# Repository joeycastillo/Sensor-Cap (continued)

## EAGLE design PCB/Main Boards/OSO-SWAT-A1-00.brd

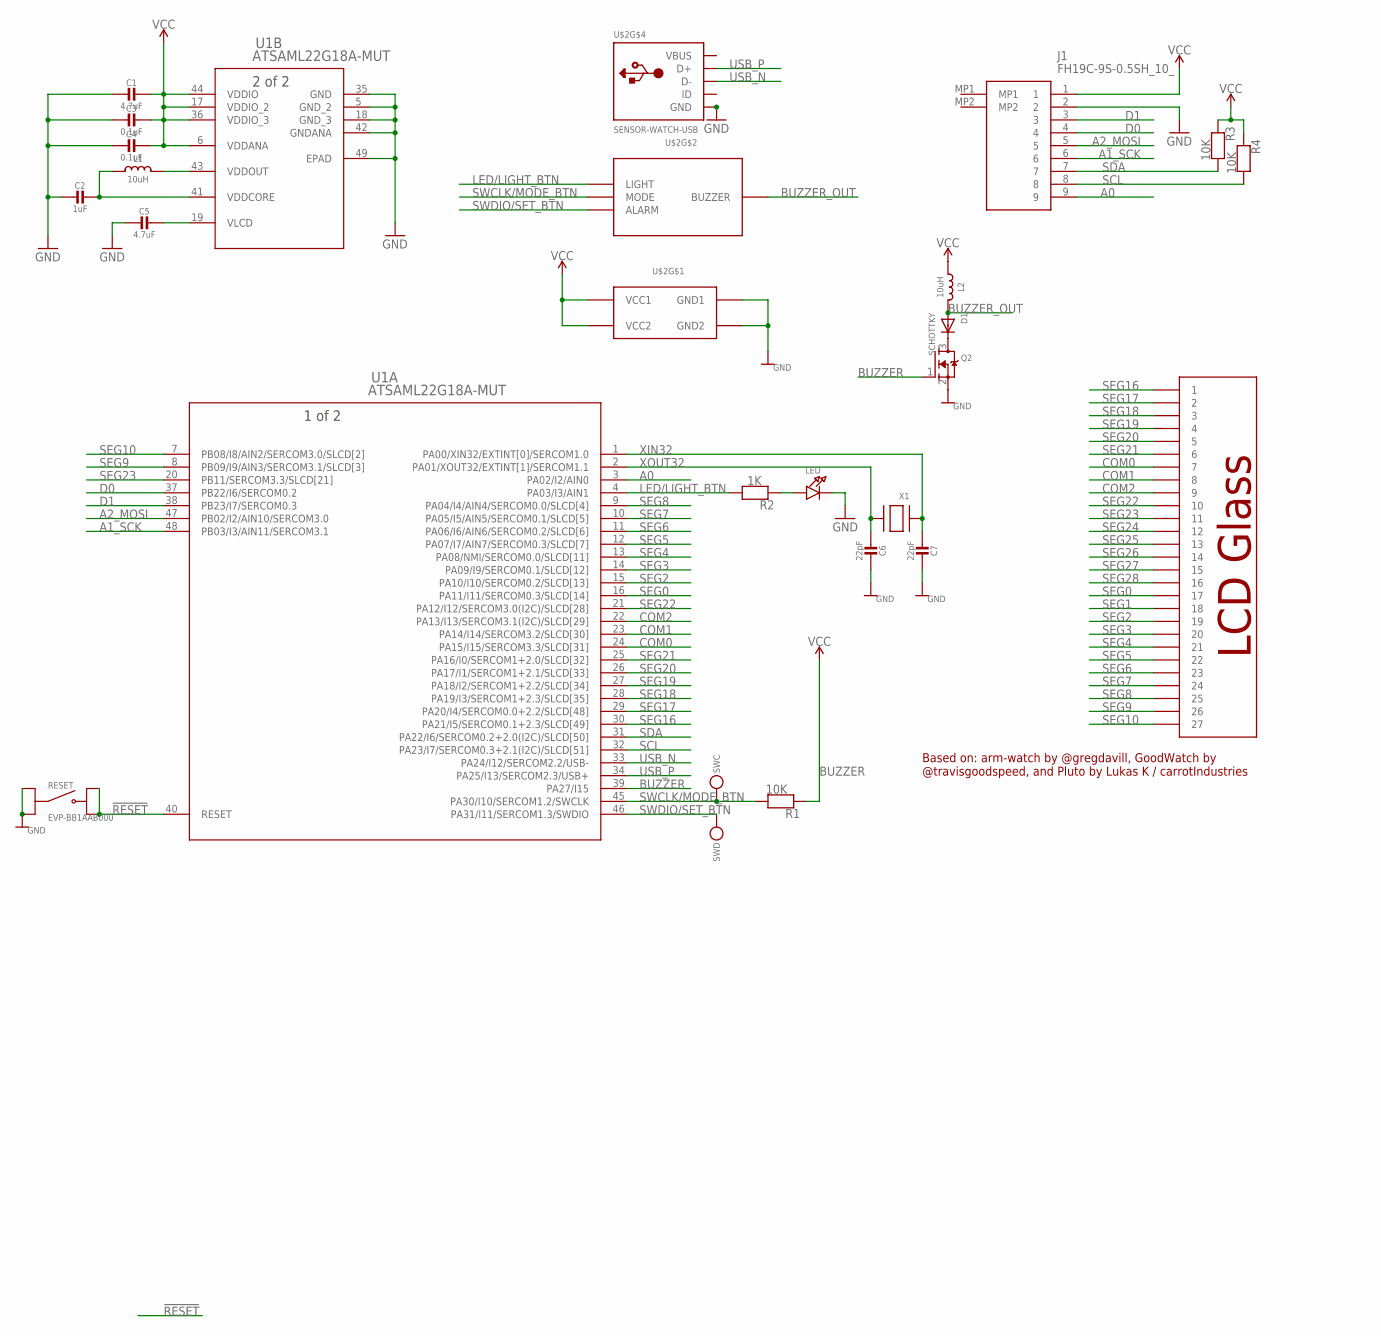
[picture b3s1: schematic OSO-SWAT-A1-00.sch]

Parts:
C1, C5: 4.7uF; _0603MP
C2: 1uF; _0603MP
C3, C4: 0.1uF; _0603MP
C6, C7: 22pF; _0603MP
D1: SCHOTTKY; SOD-323F
J1: FH19C-9S-0.5SH_10_; FH19C9S05SH10
L1, L2: 10uH; MICROBUILDER__0805MP
LED: LED0805_NOOUTLINE; CHIPLED_0805_NOOUTLINE
Q2: MOSFET-NREFLOW; SOT23-R
R1, R3, R4: 10K; _0603MP
R2: 1K; _0603MP
RESET: EVP-BB1AAB000; SW_EVP-BB1AAB000
SWC: MICROBUILDER_TESTPOINTPAD1MM; MICROBUILDER_TESTPOINT_PAD_1MM
SWD: MICROBUILDER_TESTPOINTPAD1MM; MICROBUILDER_TESTPOINT_PAD_1MM
U1: ATSAML22G18A-MUT; QFN48_7X7MC_MCH
U$2: SENSOR-WATCH-USB; CASIO-F91W-OUTLINE-USB
X1: XTAL-3.2X1.5; XTAL3215

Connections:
!RESET: RESET.B1, RESET.B2, U1.40 (RESET)
A0: J1.9, U1.3 (PA02/I2/AIN0)
A1_SCK: J1.6, U1.48 (PB03/I3/AIN11/SERCOM3.1)
A2_MOSI: J1.5, U1.47 (PB02/I2/AIN10/SERCOM3.0)
BUZZER: Q2.1 (G), U1.39 (PA27/I15)
BUZZER_OUT: D1.A, L2.2, U$2.BUZZER
COM0: U1.24 (PA15/I15/SERCOM3.3/SLCD[31]), U$2.7
COM1: U1.23 (PA14/I14/SERCOM3.2/SLCD[30]), U$2.8
COM2: U1.22 (PA13/I13/SERCOM3.1(I2C)/SLCD[29]), U$2.9
D0: J1.4, U1.37 (PB22/I6/SERCOM0.2)
D1: J1.3, U1.38 (PB23/I7/SERCOM0.3)
GND: C1.2, C2.2, C3.2, C4.2, C5.2, C6.2, C7.2, J1.2, LED.C, Q2.2 (S), RESET.A1, RESET.A2, U1.5 (GND_2), U1.18 (GND_3), U1.35 (GND), U1.42 (GNDANA), U1.49 (EPAD), U$2.GND, U$2.GND1, U$2.GND2
LED/LIGHT_BTN: R2.2, U1.4 (PA03/I3/AIN1), U$2.LIGHT
unnamed: LED.A, R2.1
unnamed: D1.C, Q2.3 (D)
SCL: J1.8, R4.2, U1.32 (PA23/I7/SERCOM0.3+2.1(I2C)/SLCD[51])
SDA: J1.7, R3.2, U1.31 (PA22/I6/SERCOM0.2+2.0(I2C)/SLCD[50])
SEG0: U1.16 (PA11/I11/SERCOM0.3/SLCD[14]), U$2.17
SEG1: U$2.18
SEG2: U1.15 (PA10/I10/SERCOM0.2/SLCD[13]), U$2.19
SEG3: U1.14 (PA09/I9/SERCOM0.1/SLCD[12]), U$2.20
SEG4: U1.13 (PA08/NMI/SERCOM0.0/SLCD[11]), U$2.21
SEG5: U1.12 (PA07/I7/AIN7/SERCOM0.3/SLCD[7]), U$2.22
SEG6: U1.11 (PA06/I6/AIN6/SERCOM0.2/SLCD[6]), U$2.23
SEG7: U1.10 (PA05/I5/AIN5/SERCOM0.1/SLCD[5]), U$2.24
SEG8: U1.9 (PA04/I4/AIN4/SERCOM0.0/SLCD[4]), U$2.25
SEG9: U1.8 (PB09/I9/AIN3/SERCOM3.1/SLCD[3]), U$2.26
SEG10: U1.7 (PB08/I8/AIN2/SERCOM3.0/SLCD[2]), U$2.27
SEG16: U1.30 (PA21/I5/SERCOM0.1+2.3/SLCD[49]), U$2.1
SEG17: U1.29 (PA20/I4/SERCOM0.0+2.2/SLCD[48]), U$2.2
SEG18: U1.28 (PA19/I3/SERCOM1+2.3/SLCD[35]), U$2.3
SEG19: U1.27 (PA18/I2/SERCOM1+2.2/SLCD[34]), U$2.4
SEG20: U1.26 (PA17/I1/SERCOM1+2.1/SLCD[33]), U$2.5
SEG21: U1.25 (PA16/I0/SERCOM1+2.0/SLCD[32]), U$2.6
SEG22: U1.21 (PA12/I12/SERCOM3.0(I2C)/SLCD[28]), U$2.10
SEG23: U1.20 (PB11/SERCOM3.3/SLCD[21]), U$2.11
SEG24: U$2.12
SEG25: U$2.13
SEG26: U$2.14
SEG27: U$2.15
SEG28: U$2.16
SWCLK/MODE_BTN: R1.2, SWC.P$1, U1.45 (PA30/I10/SERCOM1.2/SWCLK), U$2.MODE
SWDIO/SET_BTN: SWD.P$1, U1.46 (PA31/I11/SERCOM1.3/SWDIO), U$2.ALARM
USB_N: U1.33 (PA24/I12/SERCOM2.2/USB-), U$2.USB_N (D-)
USB_P: U1.34 (PA25/I13/SERCOM2.3/USB+), U$2.USB_P (D+)
VBUS: U$2.VBUS
VCC: C1.1, C3.1, C4.1, J1.1, L2.1, R1.1, R3.1, R4.1, U1.6 (VDDANA), U1.17 (VDDIO_2), U1.36 (VDDIO_3), U1.44 (VDDIO), U$2.VCC1, U$2.VCC2
VDDCORE: C2.1, L1.1, U1.41 (VDDCORE)
VDDOUT: L1.2, U1.43 (VDDOUT)
VLCD: C5.1, U1.19 (VLCD)
XIN32: C7.1, U1.1 (PA00/XIN32/EXTINT[0]/SERCOM1.0), X1.P$1
XOUT32: C6.1, U1.2 (PA01/XOUT32/EXTINT[1]/SERCOM1.1), X1.P$2

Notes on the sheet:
Based on: arm-watch by @gregdavill, GoodWatch by @travisgoodspeed, and Pluto by Lukas K / carrotIndustries

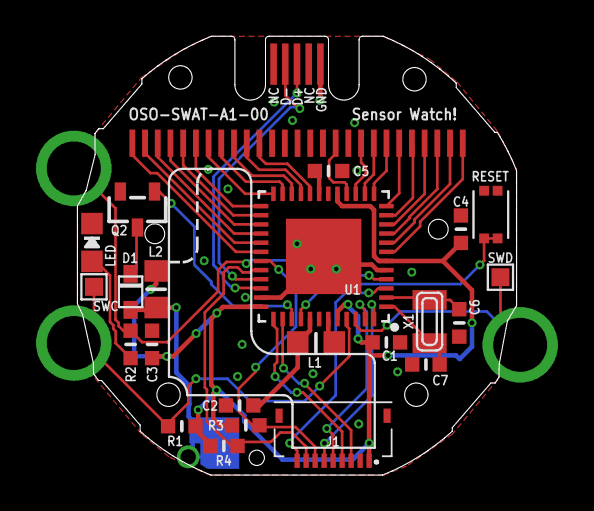
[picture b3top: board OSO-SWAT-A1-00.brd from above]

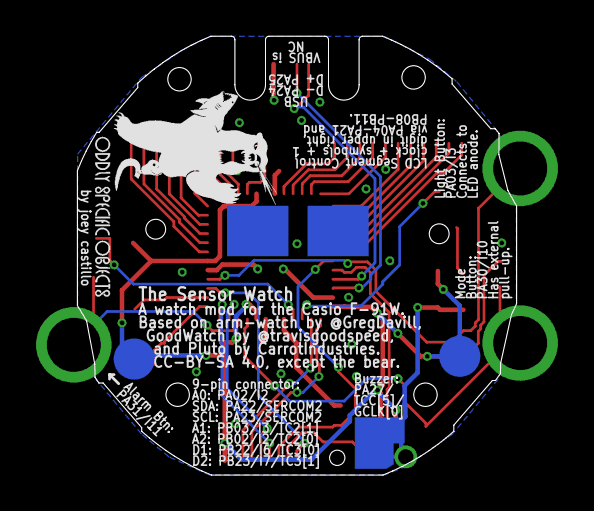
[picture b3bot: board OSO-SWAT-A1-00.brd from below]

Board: 2 copper layers, 24.4 x 24.4 mm, 25 parts (2 on the bottom side), 45 nets.

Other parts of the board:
U$5: OSO_BEAR_250X360MIL_1000DPI
U$6: OSO_WORDMARK_ONELINE_350MIL_1000DPI

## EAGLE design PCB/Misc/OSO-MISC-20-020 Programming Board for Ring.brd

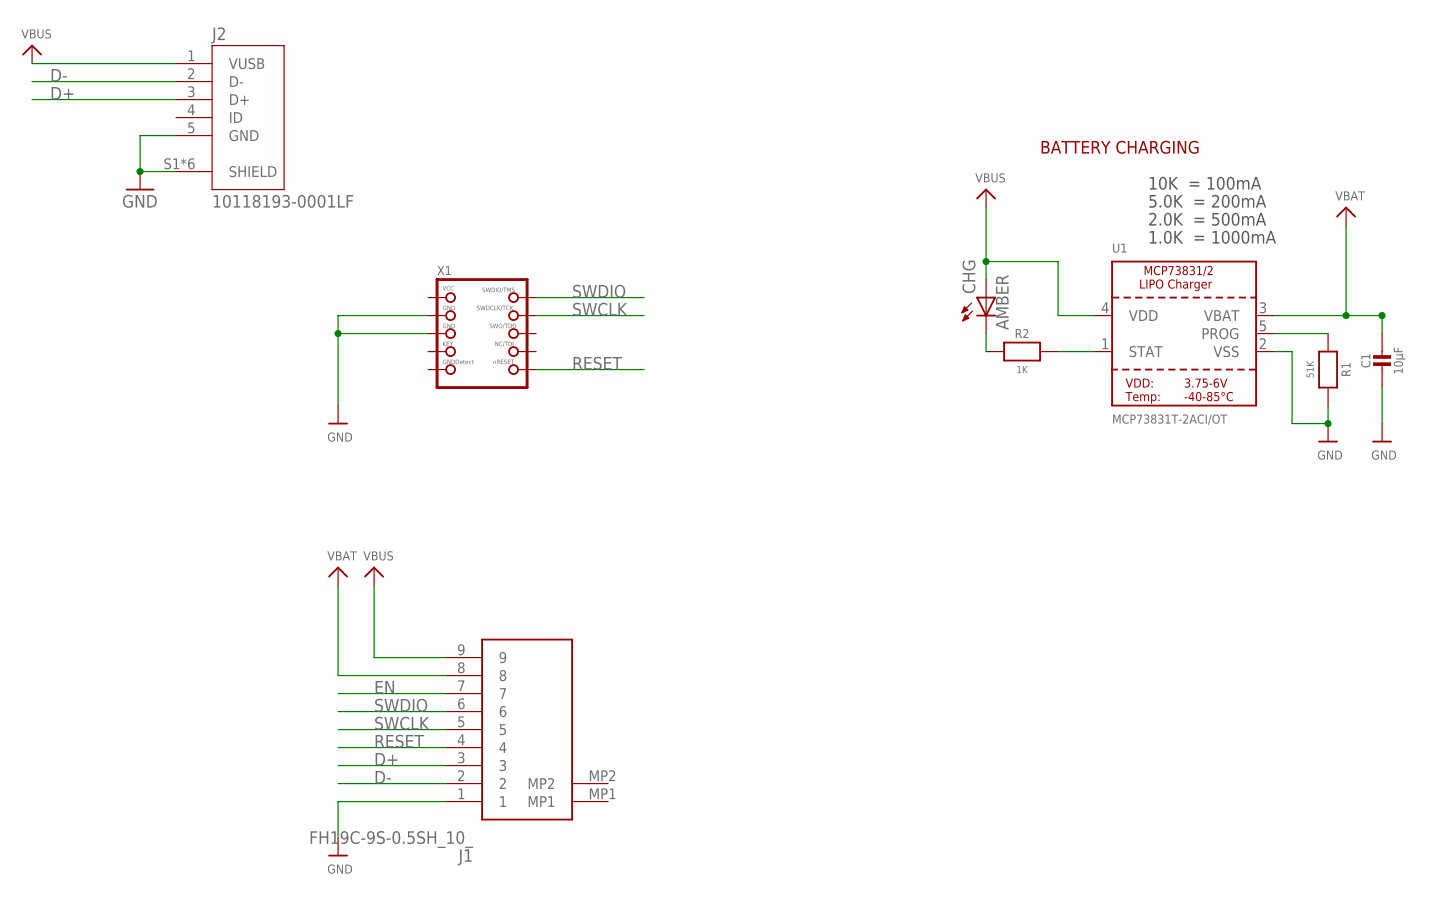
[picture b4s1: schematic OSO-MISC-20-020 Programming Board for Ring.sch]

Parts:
C1: 10µF; 0805-NO
CHG: AMBER; CHIPLED_0805
J1: FH19C-9S-0.5SH_10_; FH19C9S05SH10
J2: 10118193-0001LF; FCI_10118193-0001LF
R1: 51K; 0805-NO
R2: 1K; 0805-NO
U1: MCP73831T-2ACI/OT; SOT23-5
X1: JTAG-CORTEXBOX; 2X05_1.27MM_BOX_NOPOSTS

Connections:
D+: J1.3, J2.3 (D+)
D-: J1.2, J2.2 (D-)
EN: J1.7
GND: C1.2, J1.1, J2.5 (GND), J2.S1 (SHIELD), J2.S2 (SHIELD), J2.S3 (SHIELD), J2.S4 (SHIELD), J2.S5 (SHIELD), J2.S6 (SHIELD), R1.2, U1.2 (VSS), X1.3 (GND), X1.5 (GND)
unnamed: CHG.C, R2.1
PROG: R1.1, U1.5 (PROG)
RESET: J1.4, X1.10 (NRESET)
STAT: R2.2, U1.1 (STAT)
SWCLK: J1.5, X1.4 (SWDCLK)
SWDIO: J1.6, X1.2 (SWDIO)
VBAT: C1.1, J1.8, U1.3 (VBAT)
VBUS: CHG.A, J1.9, J2.1 (VUSB), U1.4 (VDD)
VCC: X1.1 (VCC)

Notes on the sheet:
10K = 100mA
5.0K = 200mA
2.0K = 500mA
1.0K = 1000mA
BATTERY CHARGING

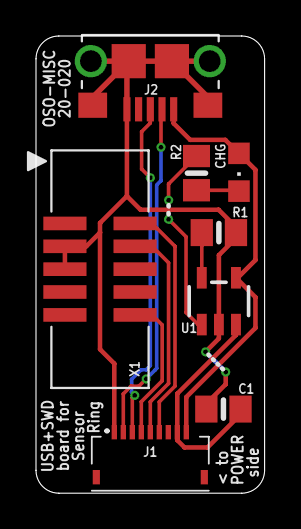
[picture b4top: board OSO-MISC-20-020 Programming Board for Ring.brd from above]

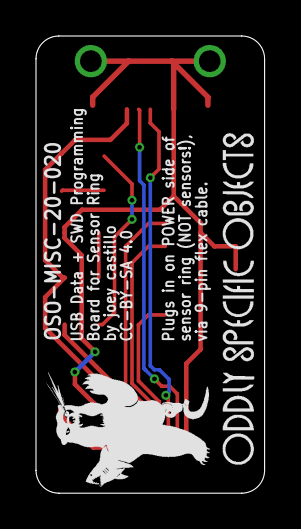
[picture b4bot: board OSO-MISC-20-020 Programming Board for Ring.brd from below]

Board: 2 copper layers, 12.7 x 25.4 mm, 10 parts (2 on the bottom side), 11 nets.

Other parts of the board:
U$1: OSO_BEAR_250X360MIL_1000DPI
U$3: OSO_WORDMARK_ONELINE_725MIL_1000DPI

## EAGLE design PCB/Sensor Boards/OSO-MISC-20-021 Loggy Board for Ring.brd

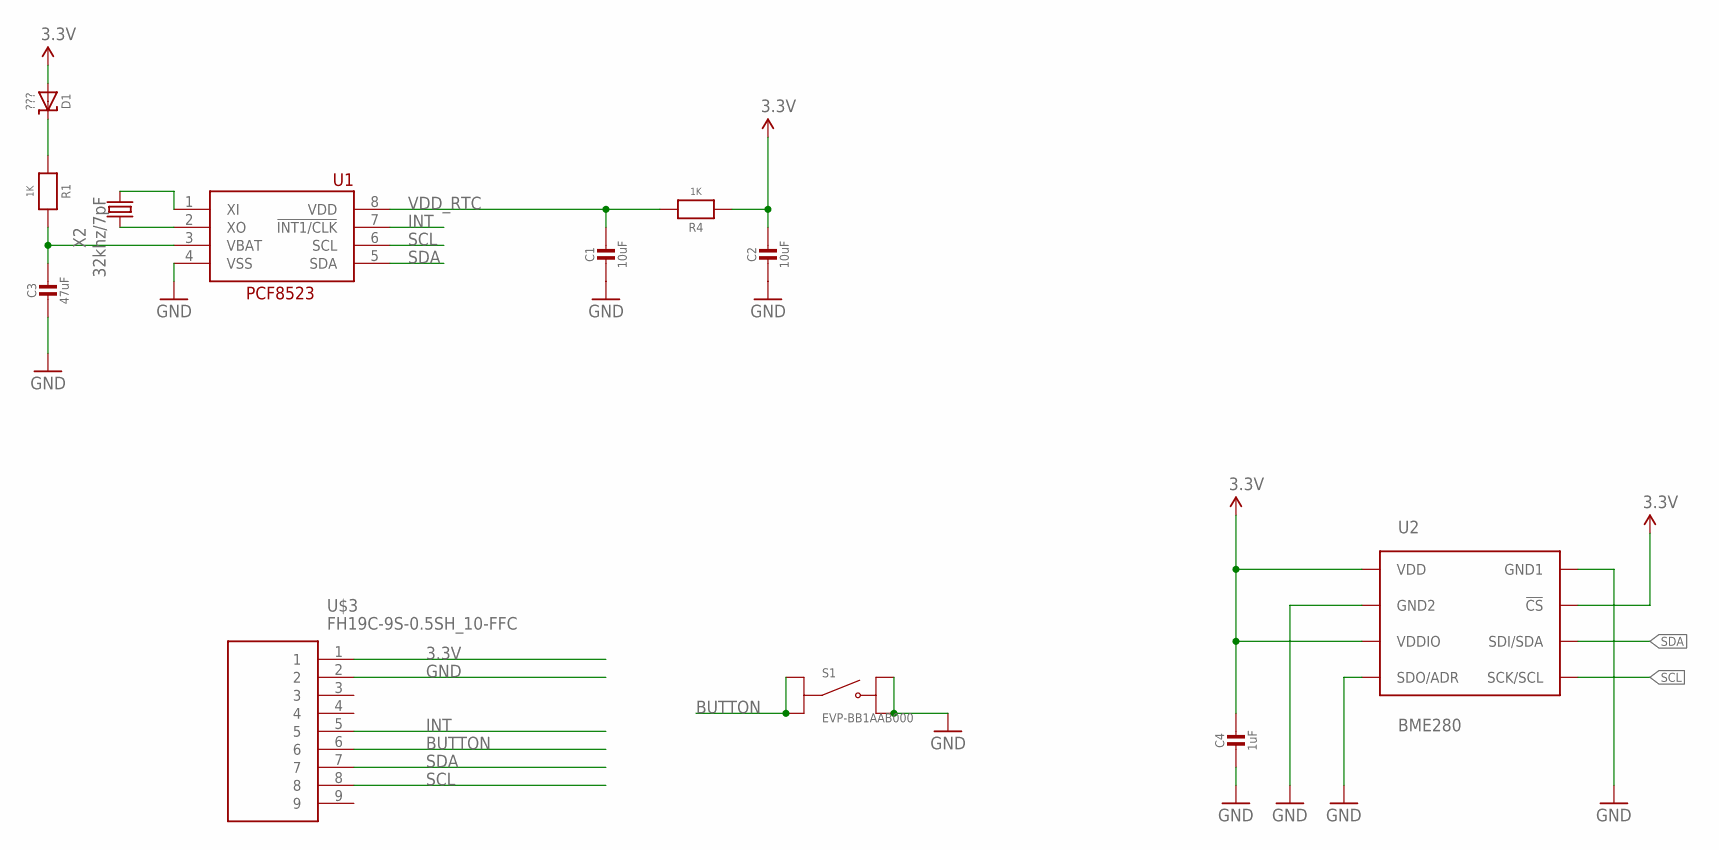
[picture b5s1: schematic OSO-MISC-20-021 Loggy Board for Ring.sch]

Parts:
C1, C2: 10uF; 0805-NO
C3: 47uF; 0805-NO
C4: 1uF; _0805MP
D1: ???; SOD-123
R1, R4: 1K; 0805-NO
S1: EVP-BB1AAB000; SW_EVP-BB1AAB000
U1: PCF8523T; SOIC8_150MIL
U2: BME280; BME280_LGA
U$3: FH19C-9S-0.5SH_10-FFC; FH19C9S05SH10-FFC
X2: 32khz/7pF; XTAL-7015

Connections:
3.3V: C2.1, C4.1, D1.A, R4.1, U2.P$2 (!CS), U2.P$6 (VDDIO), U2.P$8 (VDD), U$3.1
BUTTON: S1.A1, S1.A2, U$3.6
GND: C1.2, C2.2, C3.2, C4.2, S1.B1, S1.B2, U1.4 (VSS), U2.P$1 (GND1), U2.P$5 (SDO/ADR), U2.P$7 (GND2), U$3.2
INT: U1.7 (!INT1/CLK), U$3.5
unnamed: D1.C, R1.1
unnamed: C3.1, R1.2, U1.3 (VBAT)
unnamed: U1.1 (XI), X2.1
unnamed: U1.2 (XO), X2.4 (2)
SCL: U1.6 (SCL), U2.P$4 (SCK/SCL), U$3.8
SDA: U1.5 (SDA), U2.P$3 (SDI/SDA), U$3.7
VDD_RTC: C1.1, R4.2, U1.8 (VDD)

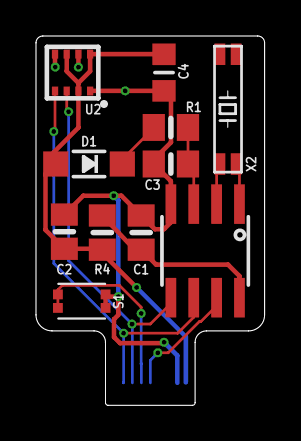
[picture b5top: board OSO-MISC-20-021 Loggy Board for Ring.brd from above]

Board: 2 copper layers, 12.7 x 20.5 mm, 12 parts (0 on the bottom side), 11 nets.

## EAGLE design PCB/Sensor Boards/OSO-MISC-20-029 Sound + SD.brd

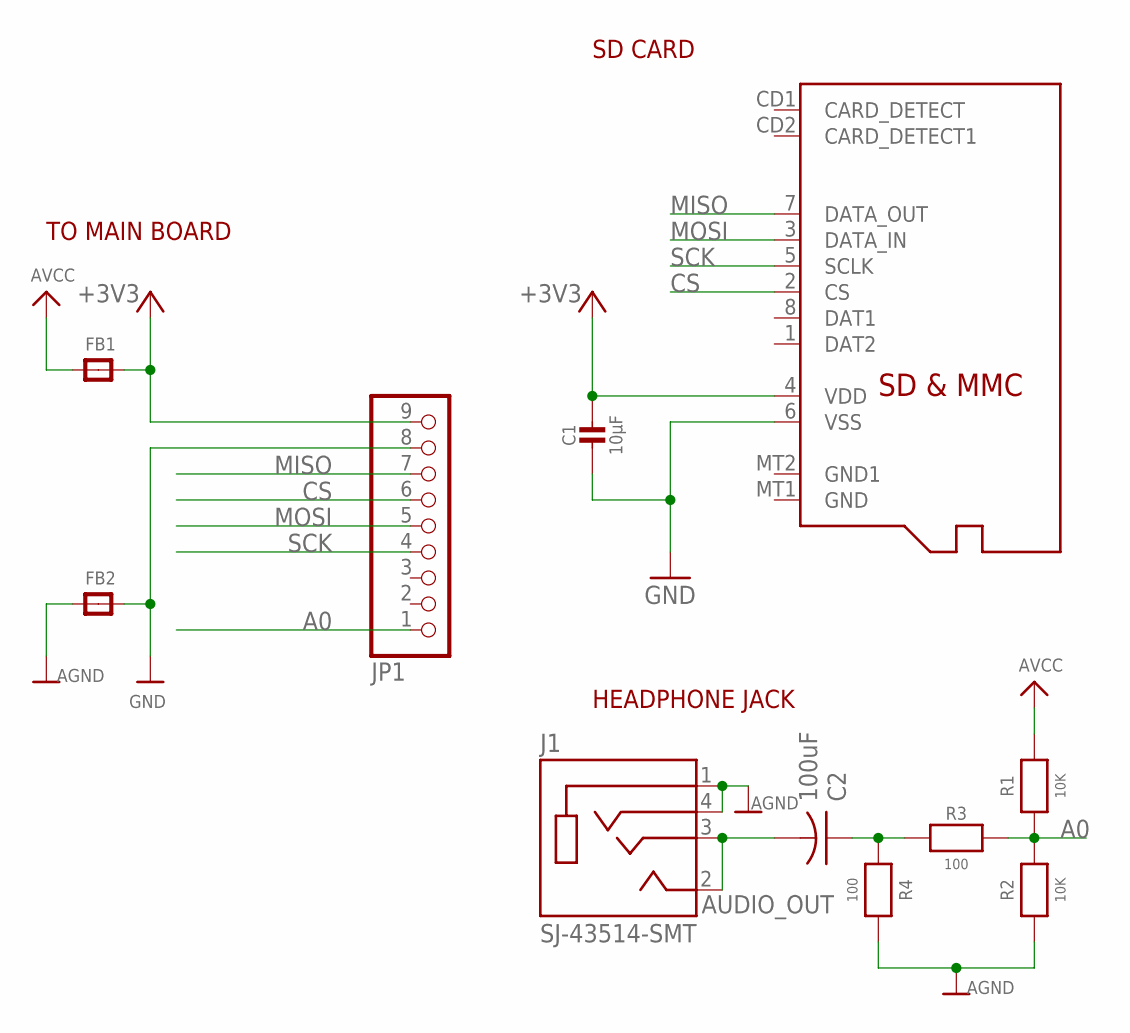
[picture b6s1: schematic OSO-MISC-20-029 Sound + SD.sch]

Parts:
C1: 10µF; 0805-NO
C2: 100uF; C1210
FB1, FB2: FERRITE0805; 0805
J1: SJ-43514-SMT; CUI_SJ-43514-SMT
JP1: HEADER-1X9_JSTSH; JST_SH9
MICROSD: MICROSD
R1, R2: 10K; _0805MP
R3, R4: 100; _0805MP

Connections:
+3V3: C1.1, FB1.2, JP1.9, MICROSD.4 (VDD)
A0: JP1.1, R1.2, R2.1, R3.1
AGND: FB2.1, J1.1 (SLEEVE), J1.4 (RING2), R2.2, R4.1
AUDIO_OUT: C2.2, J1.2 (TIP), J1.3 (RING1)
AVCC: FB1.1, R1.1
CS: JP1.6, MICROSD.2 (CS)
GND: C1.2, FB2.2, JP1.8, MICROSD.6 (VSS)
MISO: JP1.7, MICROSD.7 (DATA_OUT)
MOSI: JP1.5, MICROSD.3 (DATA_IN)
unnamed: C2.1, R3.2, R4.2
SCK: JP1.4, MICROSD.5 (SCLK)

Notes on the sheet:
SD CARD
TO MAIN BOARD
HEADPHONE JACK

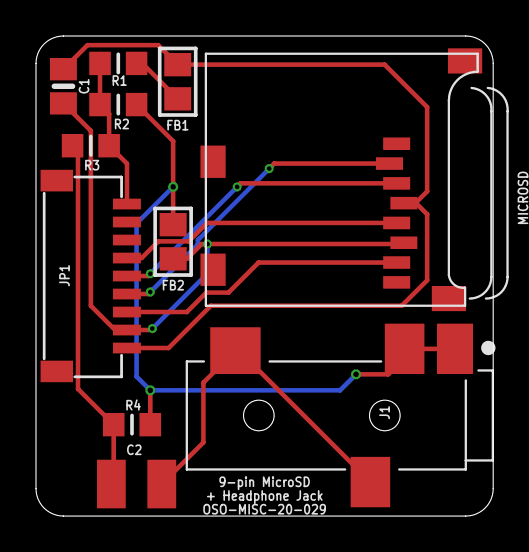
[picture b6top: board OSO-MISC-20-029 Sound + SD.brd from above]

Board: 2 copper layers, 25.4 x 26.7 mm, 13 parts (2 on the bottom side), 11 nets.

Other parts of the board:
U$4: OSO_BEAR_525X750MIL_1000DPI
U$5: OSO_WORDMARK_ONELINE_725MIL_1000DPI

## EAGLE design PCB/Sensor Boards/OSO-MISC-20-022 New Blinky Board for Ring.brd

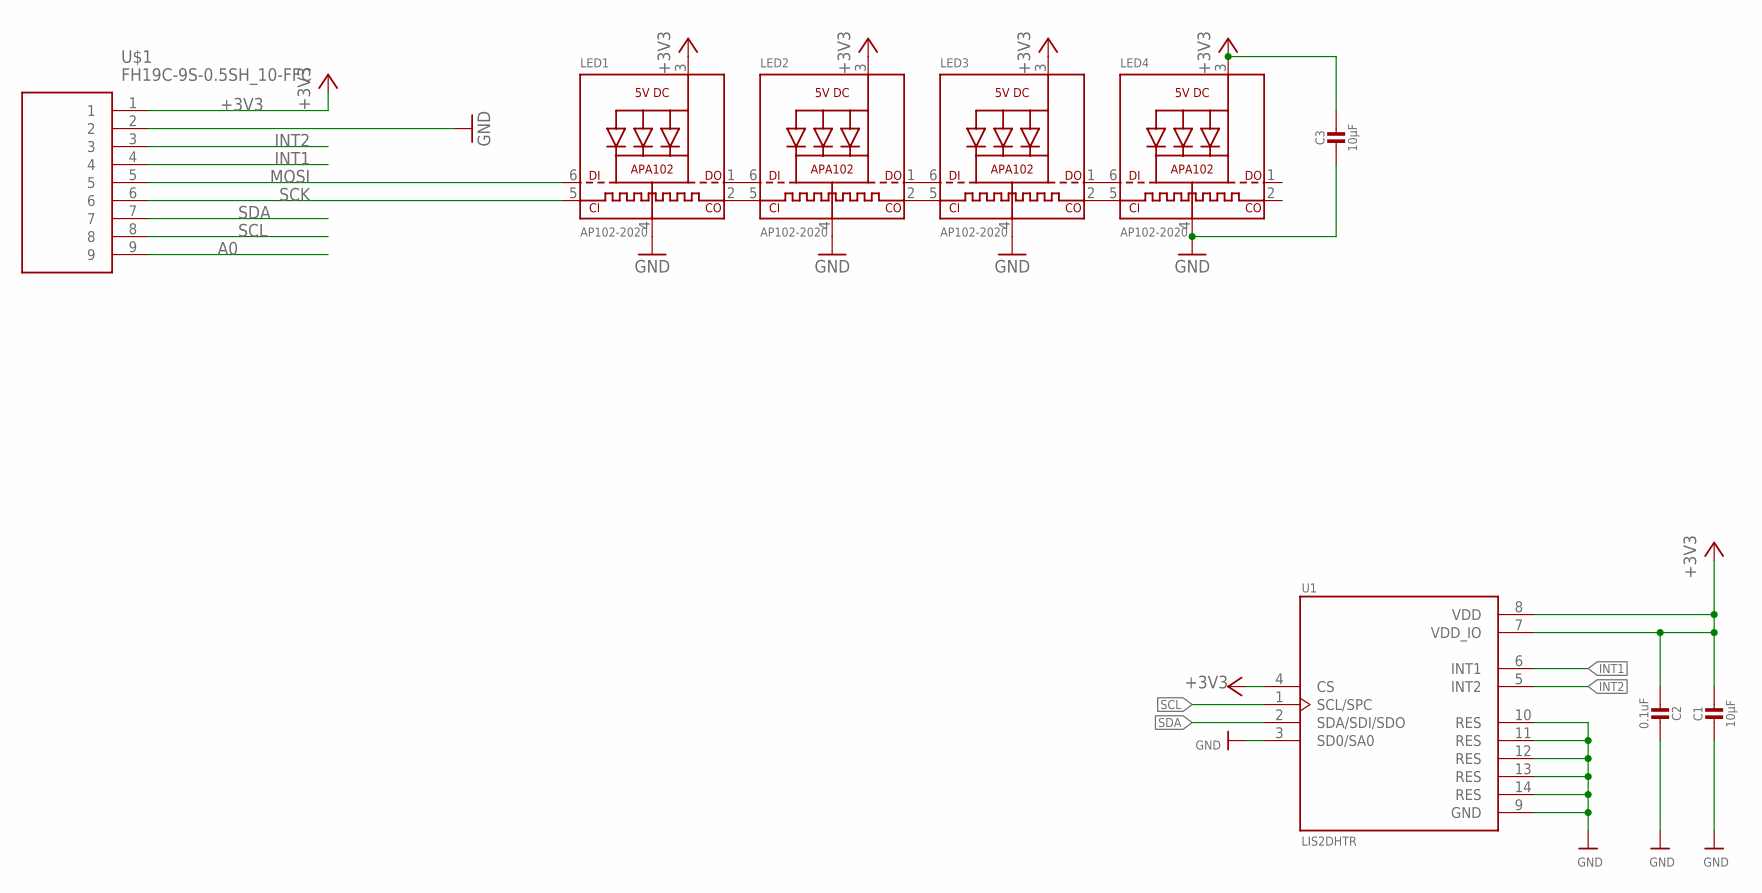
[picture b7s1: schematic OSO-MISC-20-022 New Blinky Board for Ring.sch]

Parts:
C1: 10µF; 0805_10MGAP
C2: 0.1uF; 0805-NO
C3: 10µF; 0805-NO
LED1, LED2, LED3, LED4: AP102-2020; APA102_2020
U1: LIS2DHTR; PQFN35P200X200X100-14N
U$1: FH19C-9S-0.5SH_10-FFC; FH19C9S05SH10-FFC

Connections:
+3V3: C1.1, C2.2, C3.1, LED1.3 (VDD), LED2.3 (VDD), LED3.3 (VDD), LED4.3 (VDD), U1.4 (CS), U1.7 (VDD_IO), U1.8 (VDD), U$1.1
A0: U$1.9
GND: C1.2, C2.1, C3.2, LED1.4 (GND), LED2.4 (GND), LED3.4 (GND), LED4.4 (GND), U1.3 (SD0/SA0), U1.9 (GND), U1.10 (RES), U1.11 (RES), U1.12 (RES), U1.13 (RES), U1.14 (RES), U$1.2
INT1: U1.6 (INT1), U$1.4
INT2: U1.5 (INT2), U$1.3
MOSI: LED1.6 (DI), U$1.5
unnamed: LED1.1 (DO), LED2.6 (DI)
unnamed: LED1.2 (CKO), LED2.5 (CKI)
unnamed: LED2.1 (DO), LED3.6 (DI)
unnamed: LED2.2 (CKO), LED3.5 (CKI)
unnamed: LED3.1 (DO), LED4.6 (DI)
unnamed: LED3.2 (CKO), LED4.5 (CKI)
SCK: LED1.5 (CKI), U$1.6
SCL: U1.1 (SCL/SPC), U$1.8
SDA: U1.2 (SDA/SDI/SDO), U$1.7

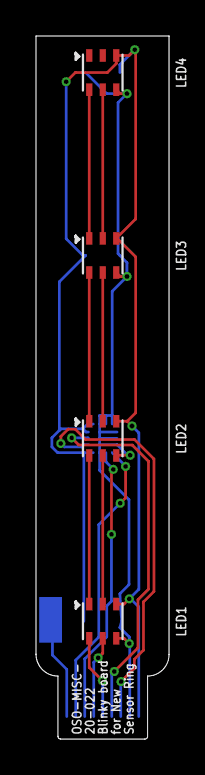
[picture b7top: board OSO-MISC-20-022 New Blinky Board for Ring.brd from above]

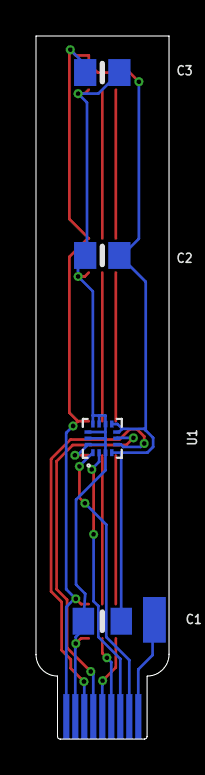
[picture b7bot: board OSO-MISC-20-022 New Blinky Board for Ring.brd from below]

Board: 2 copper layers, 7.4 x 39.1 mm, 9 parts (4 on the bottom side), 14 nets.

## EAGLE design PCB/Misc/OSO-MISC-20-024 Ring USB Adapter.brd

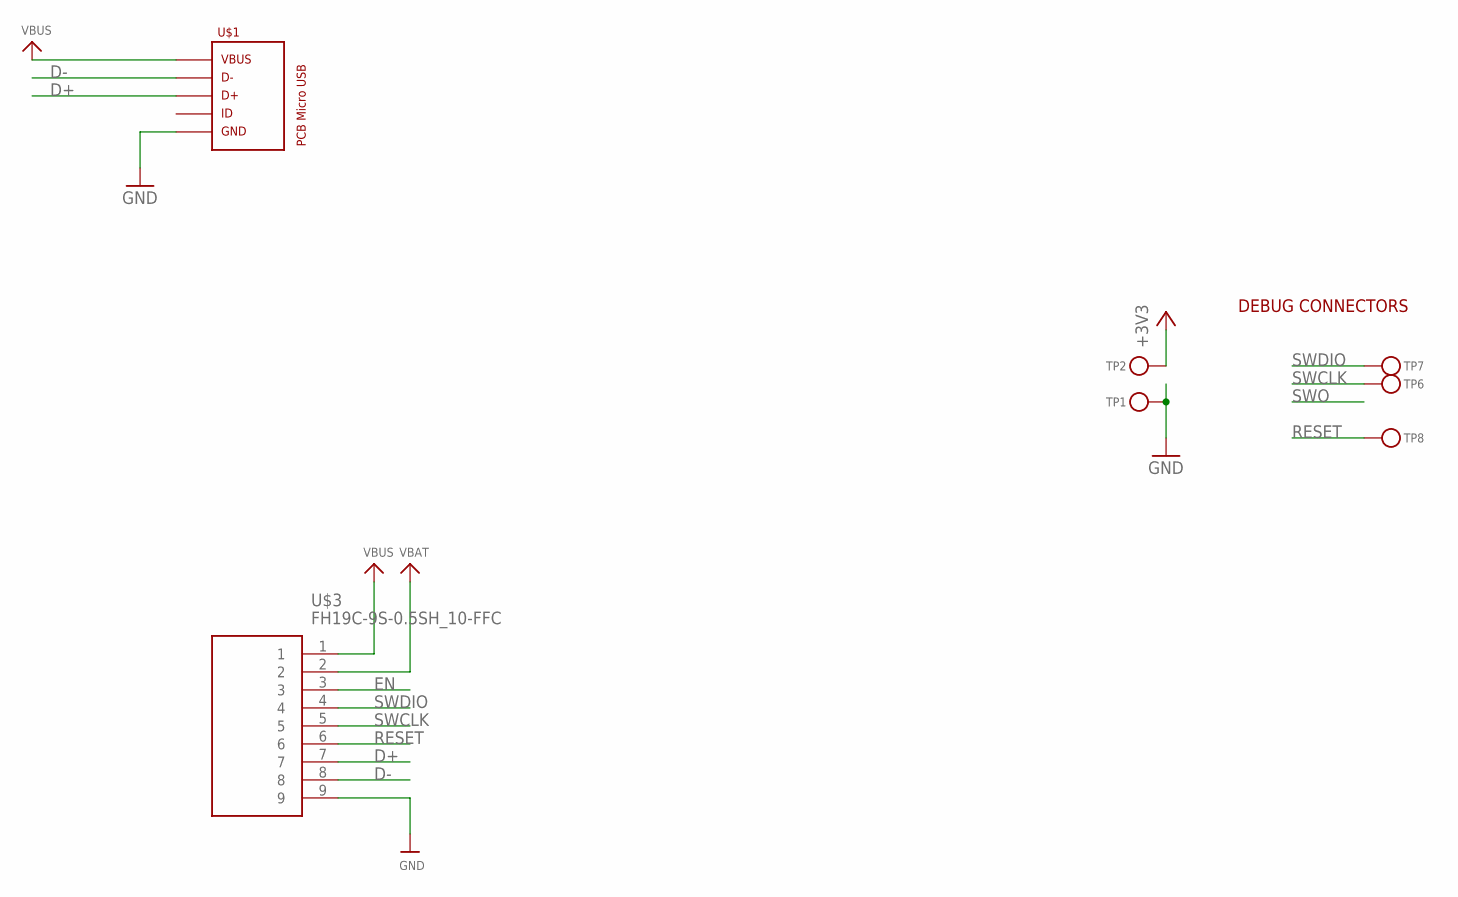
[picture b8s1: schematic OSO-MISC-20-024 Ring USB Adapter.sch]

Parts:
TP1, TP2, TP6, TP7, TP8: TESTPOINTROUND2MMNO; TESTPOINT_ROUND_2MM_NO
U$1: PCB_MICRO_USB_BSS_100; USB_TYPE_B_SS_100
U$3: FH19C-9S-0.5SH_10-FFC; FH19C9S05SH10-FFC

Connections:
+3V3: TP2.P$1
D+: U$1.3, U$3.7
D-: U$1.2, U$3.8
EN: U$3.3
GND: TP1.P$1, U$1.5, U$3.9
RESET: TP8.P$1, U$3.6
SWCLK: TP6.P$1, U$3.5
SWDIO: TP7.P$1, U$3.4
VBAT: U$3.2
VBUS: U$1.1, U$3.1

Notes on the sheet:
DEBUG CONNECTORS

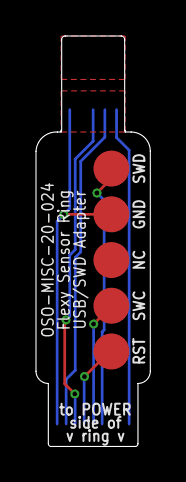
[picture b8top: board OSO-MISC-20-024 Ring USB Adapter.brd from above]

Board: 2 copper layers, 6.3 x 22.8 mm, 7 parts (1 on the bottom side), 7 nets.

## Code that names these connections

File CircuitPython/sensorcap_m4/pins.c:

#include "shared-bindings/board/__init__.h"

#include "boards/board.h"

STATIC const mp_rom_map_elem_t board_global_dict_table[] = {
    // 9-pin connector
    { MP_OBJ_NEW_QSTR(MP_QSTR_A0),  MP_ROM_PTR(&pin_PA05) },
    { MP_OBJ_NEW_QSTR(MP_QSTR_A1),  MP_ROM_PTR(&pin_PA07) },
    { MP_OBJ_NEW_QSTR(MP_QSTR_A2),  MP_ROM_PTR(&pin_PA06) },
    { MP_OBJ_NEW_QSTR(MP_QSTR_A3),  MP_ROM_PTR(&pin_PB09) },
    { MP_OBJ_NEW_QSTR(MP_QSTR_A4),  MP_ROM_PTR(&pin_PA04) },
    { MP_OBJ_NEW_QSTR(MP_QSTR_D0),  MP_ROM_PTR(&pin_PB09) },
    { MP_OBJ_NEW_QSTR(MP_QSTR_D1),  MP_ROM_PTR(&pin_PA04) },
    
    // I2C
    { MP_OBJ_NEW_QSTR(MP_QSTR_SDA),  MP_ROM_PTR(&pin_PA12) },
    { MP_OBJ_NEW_QSTR(MP_QSTR_SCL),  MP_ROM_PTR(&pin_PA13) },

    // Blinkenlights
    { MP_OBJ_NEW_QSTR(MP_QSTR_LED),  MP_ROM_PTR(&pin_PA31) },
    { MP_OBJ_NEW_QSTR(MP_QSTR_NEOPIXEL),  MP_ROM_PTR(&pin_PB22) },

    // On-board audio
    { MP_ROM_QSTR(MP_QSTR_SPEAKER), MP_ROM_PTR(&pin_PA02) },
    { MP_ROM_QSTR(MP_QSTR_SPEAKER_ENABLE), MP_ROM_PTR(&pin_PB23) },
    
    // On-board sensors
    { MP_ROM_QSTR(MP_QSTR_TEMPERATURE), MP_ROM_PTR(&pin_PB02) },
    { MP_ROM_QSTR(MP_QSTR_VOLTAGE_MONITOR), MP_ROM_PTR(&pin_PB08) },
    { MP_ROM_QSTR(MP_QSTR_BATTERY), MP_ROM_PTR(&pin_PB08) },
    { MP_ROM_QSTR(MP_QSTR_RTC_INTERRUPT), MP_ROM_PTR(&pin_PA15) },

    // On-board Buttons
    { MP_OBJ_NEW_QSTR(MP_QSTR_BUTTON_0),  MP_ROM_PTR(&pin_PA27) },
    { MP_OBJ_NEW_QSTR(MP_QSTR_BUTTON_1),  MP_ROM_PTR(&pin_PA30) },

    // Ports and accessories
    { MP_ROM_QSTR(MP_QSTR_STEMMA), MP_ROM_PTR(&pin_PA14) },
    { MP_OBJ_NEW_QSTR(MP_QSTR_ACCESSORY_IO_0),  MP_ROM_PTR(&pin_PA20) },
    { MP_OBJ_NEW_QSTR(MP_QSTR_ACCESSORY_IO_1),  MP_ROM_PTR(&pin_PA19) },
    { MP_OBJ_NEW_QSTR(MP_QSTR_ACCESSORY_ENABLE),  MP_ROM_PTR(&pin_PA18) },
    { MP_OBJ_NEW_QSTR(MP_QSTR_ACCESSORY_RESET),  MP_ROM_PTR(&pin_PA21) },
    { MP_OBJ_NEW_QSTR(MP_QSTR_USBID),  MP_ROM_PTR(&pin_PA23) },

    // SPI — this is on the 2x4 pin header as an alternative to the UART. 
    // No hardware SPI on the 9-pin!
    { MP_OBJ_NEW_QSTR(MP_QSTR_SCK),  MP_ROM_PTR(&pin_PA17) },
    { MP_OBJ_NEW_QSTR(MP_QSTR_MISO),  MP_ROM_PTR(&pin_PA18) },
    { MP_OBJ_NEW_QSTR(MP_QSTR_MOSI),  MP_ROM_PTR(&pin_PA19) },

    // UART
    { MP_OBJ_NEW_QSTR(MP_QSTR_RX),  MP_ROM_PTR(&pin_PA19) },
    { MP_OBJ_NEW_QSTR(MP_QSTR_TX),  MP_ROM_PTR(&pin_PA18) },

    { MP_ROM_QSTR(MP_QSTR_I2C), MP_ROM_PTR(&board_i2c_obj) },
    { MP_ROM_QSTR(MP_QSTR_SPI), MP_ROM_PTR(&board_spi_obj) },
    { MP_ROM_QSTR(MP_QSTR_UART), MP_ROM_PTR(&board_uart_obj) },
};
MP_DEFINE_CONST_DICT(board_module_globals, board_global_dict_table);

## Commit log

2020-05-01 first actual commit
2020-05-01 add documentation to pcb folder
2020-05-01 A1 rev 02: add i2c pull-ups
2020-05-04 CHG and FUL now separate LEDs
2020-05-04 some miscellaneous helper boards
2020-05-14 new ideas
2020-06-11 add descriptive filenames for sensor boards
2020-06-11 rev 2 of sensor cap
2020-07-29 june projects
2020-08-02 organize schematic, update some values
2020-08-02 update readme for sensor candle
2020-09-29 sensor ring experiment
2020-11-06 sensor ring: add flexy charge/programming board
2020-12-07 add 4- and 6-layer sensor ring boards
2020-12-27 add the PyCorder
2020-12-27 december stuff
2021-01-11 sensor watch experiment
2021-01-18 fix capacitor value
2021-01-18 starting work on pycorder rev 02
2021-02-10 watch stuff
2021-02-10 remove watch rev 00
2021-02-15 fail fail fail fail fail
2021-03-04 new pycorder and sensor watch
2021-03-18 remove pycorder, now lives at https://github.com/joeycastillo/pycorder
2021-04-10 move sensor watch to https://github.com/joeycastillo/Sensor-Watch
